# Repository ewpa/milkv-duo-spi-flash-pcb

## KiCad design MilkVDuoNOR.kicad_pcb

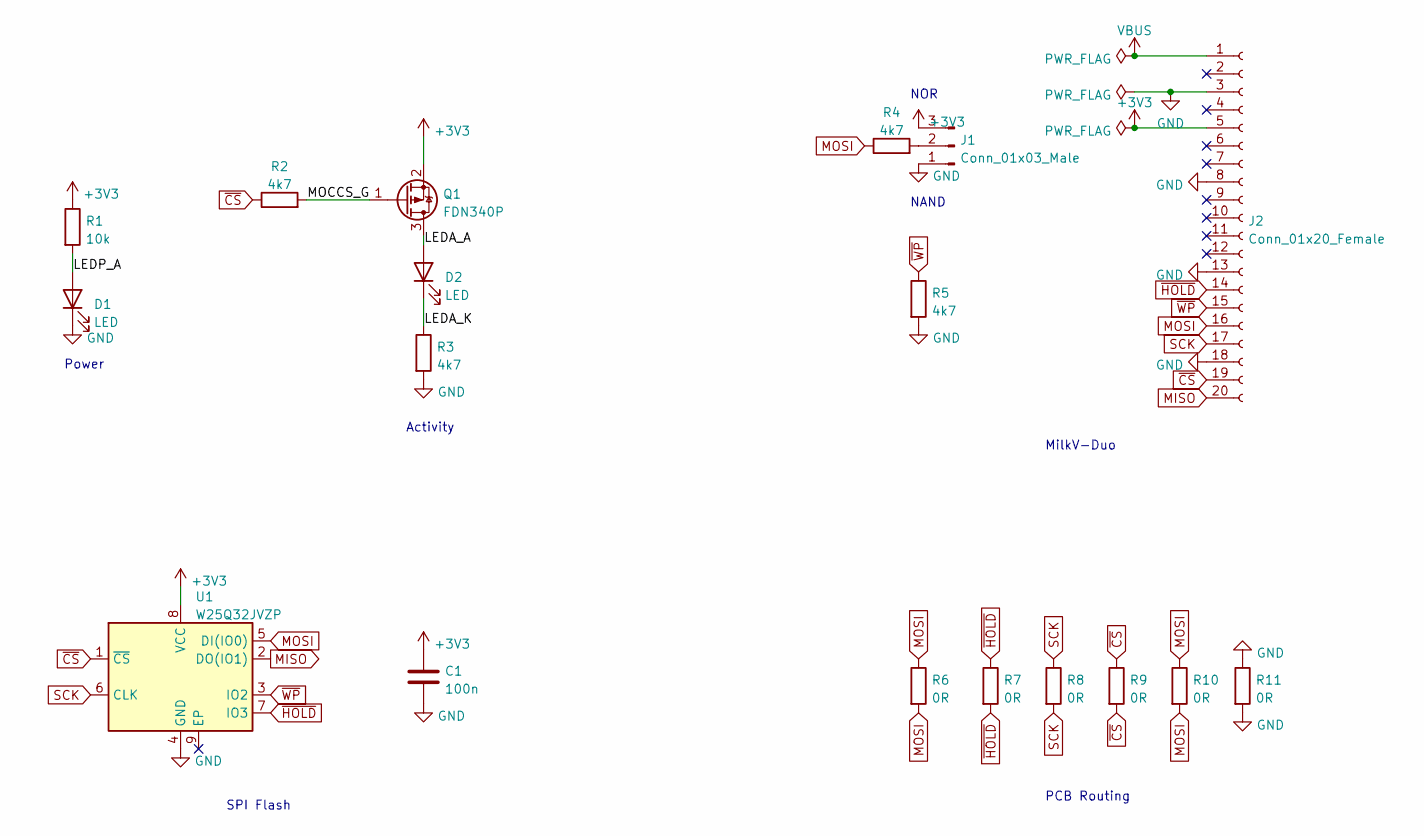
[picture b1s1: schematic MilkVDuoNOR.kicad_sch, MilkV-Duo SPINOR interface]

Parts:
C1: 100n; C_1206_3216Metric
D1, D2: LED; LED_1206_3216Metric
J1: Conn_01x03_Male; PinHeader_1x03_P2.54mm_Vertical
J2: Conn_01x20_Female; PinSocket_1x20_P2.54mm_Vertical
Q1: FDN340P; SOT-23
R1: 10k; R_1206_3216Metric
R2, R3, R4, R5: 4k7; R_1206_3216Metric
R6, R7, R8, R9, R10, R11: 0R; R_1206_3216Metric
U1: W25Q32JVZP; WSON-8-1EP_8x6mm_P1.27mm_EP3.4x4.3mm

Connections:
+3V3: C1.1, J1.3, J2.5, Q1.2 (S), R1.1, U1.8 (VCC)
/LEDA_A: D2.2 (A), Q1.3 (D)
/LEDA_K: D2.1 (K), R3.1
/LEDP_A: D1.2 (A), R1.2
/MOCCS_G: Q1.1 (G), R2.2
GND: C1.2, D1.1 (K), J1.1, J2.3, J2.8, J2.13, J2.18, R3.2, R5.2, R11.1, R11.2, U1.4 (GND)
MISO: J2.20, U1.2 (DO(IO1))
MOSI: J2.16, R4.1, R6.1, R6.2, R10.1, R10.2, U1.5 (DI(IO0))
unnamed: J1.2, R4.2
SCK: J2.17, R8.1, R8.2, U1.6 (CLK)
VBUS: J2.1
~CS: J2.19, R2.1, R9.1, R9.2, U1.1 (~CS)
~HOLD: J2.14, R7.1, R7.2, U1.7 (IO3)
~WP: J2.15, R5.1, U1.3 (IO2)

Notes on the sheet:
NOR
SPI Flash
Activity
MilkV-Duo
PCB Routing
NAND
Power

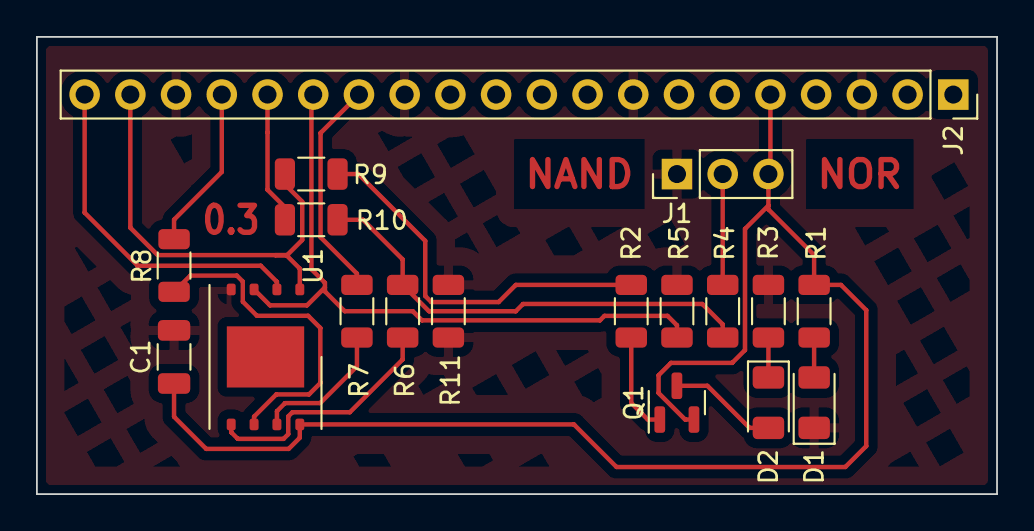
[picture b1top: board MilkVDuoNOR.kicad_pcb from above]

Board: 2 copper layers, 53.3 x 25.4 mm, 18 parts (0 on the bottom side), 13 nets.

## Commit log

2023-09-15 MilkV-Duo SPINOR/NAND flash interface, suitable for home manufacture.
